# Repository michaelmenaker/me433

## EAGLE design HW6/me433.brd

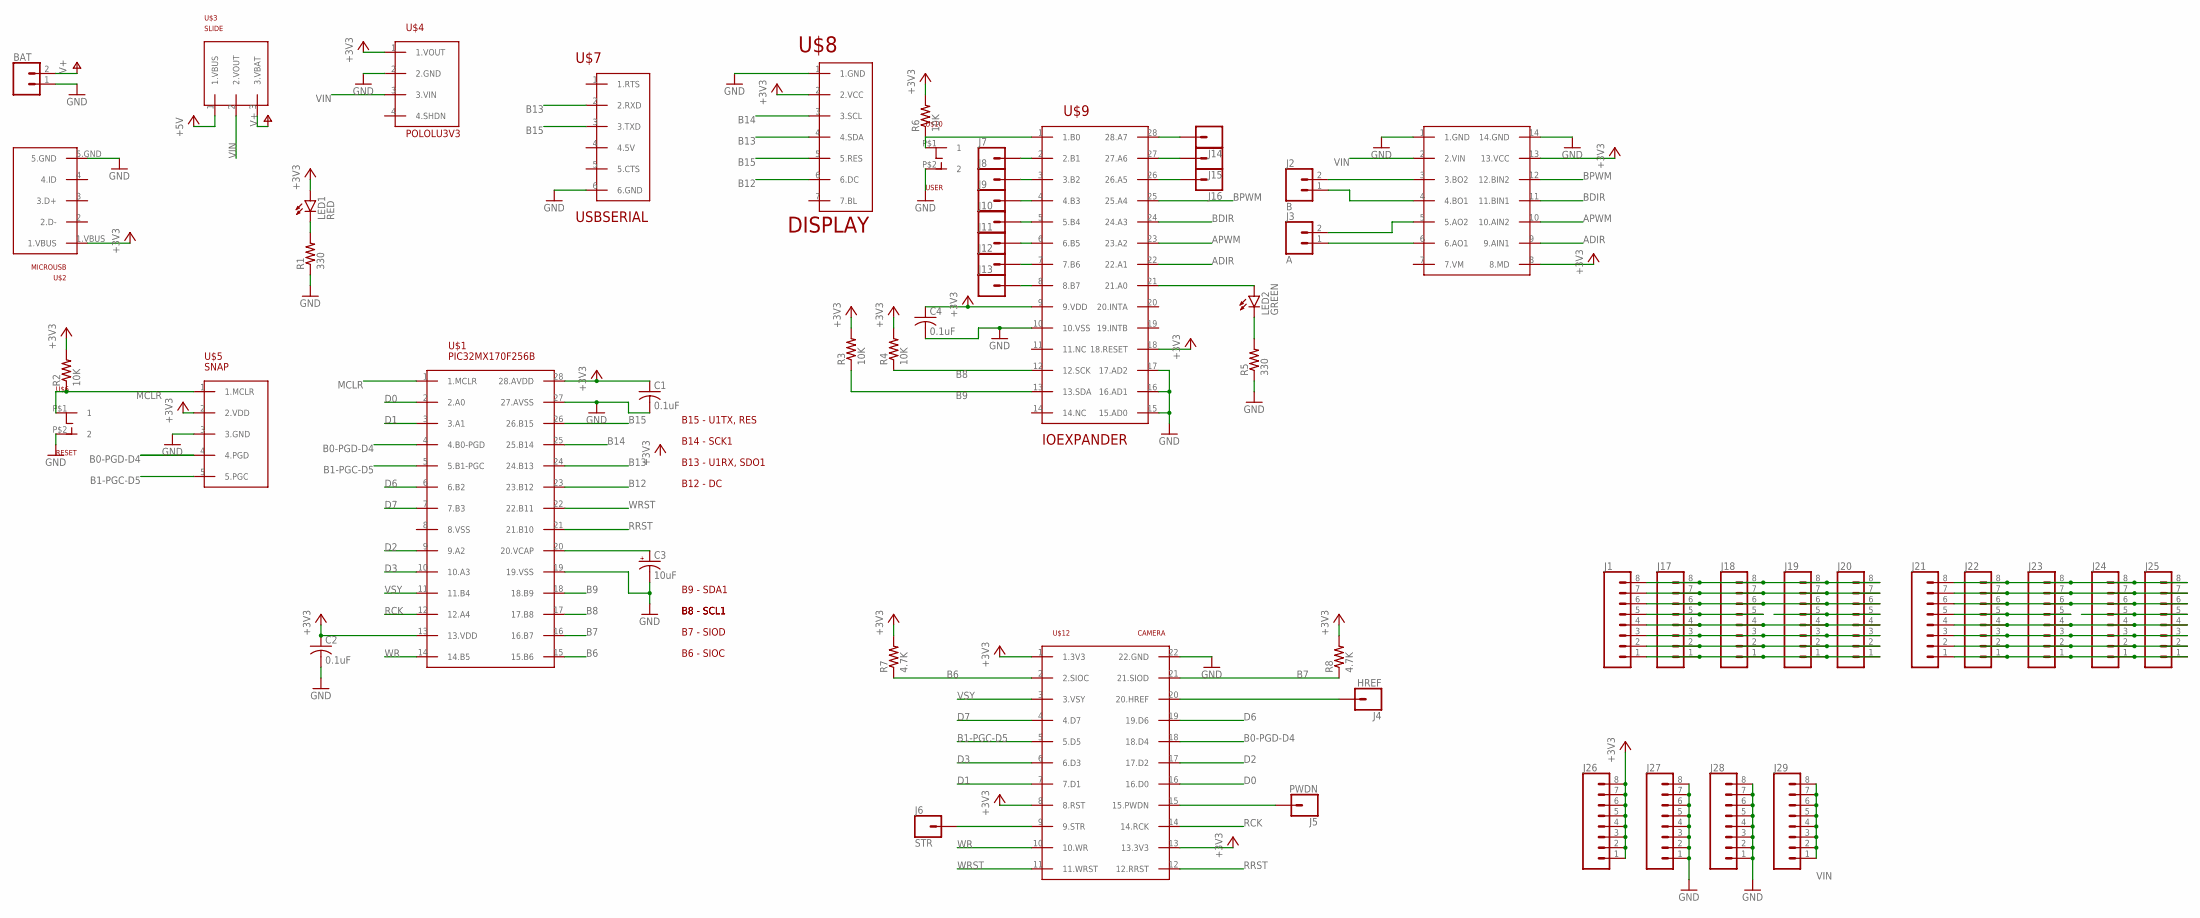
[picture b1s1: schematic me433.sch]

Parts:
BAT: CONN_02; 1X02
C1, C2, C4: 0.1uF; C025-030X050
C3: 10uF; B45181B
J1, J17, J18, J19, J20, J21, J22, J23, J24, J25, J26, J27, J28, J29: CONN_08"; 1X08
J2: B; 1X02
J3: A; 1X02
J4: HREF; 1X01
J5: PWDN; 1X01
J6: STR; 1X01
J7, J8, J9, J10, J11, J12, J13, J14, J15, J16: CONN_01; 1X01
LED1: RED; LED3MM
LED2: GREEN; LED3MM
R1, R5: 330; 0207/10
R2, R3, R4, R6: 10K; 0207/10
R7, R8: 4.7K; 0207/10
U$1: PIC32MX170F256B; DIL28-3
U$2: MICROUSB
U$3: SLIDE
U$4: POLOLU3V3
U$5: SNAP
U$6: RESET; PUSH
U$7: USBSERIAL
U$8: DISPLAY
U$9: IOEXPANDER
U$10: USER; PUSH
U$11: HBRIDGE
U$12: CAMERA

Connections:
+3V1: LED2.A, U$9.21 (21.A0)
+3V3: C1.1, C2.1, C4.1, J26.1, J26.2, J26.3, J26.4, J26.5, J26.6, J26.7, J26.8, LED1.A, R2.2, R3.2, R4.2, R6.2, R7.2, R8.2, U$1.13 (13.VDD), U$1.28 (28.AVDD), U$2.1.VBUS, U$4.1 (1.VOUT), U$5.2 (2.VDD), U$8.2 (2.VCC), U$9.9 (9.VDD), U$9.18 (18.RESET), U$11.8 (8.MD), U$11.13 (13.VCC), U$12.1 (1.3V3), U$12.8 (8.RST), U$12.13 (13.3V3)
+5V: U$3.1 (1.VBUS)
ADIR: U$9.22 (22.A1), U$11.9 (9.AIN1)
APWM: U$9.23 (23.A2), U$11.10 (10.AIN2)
B0-PGD-D4: U$1.4 (4.B0-PGD), U$5.4 (4.PGD), U$12.18 (18.D4)
B1-PGC-D5: U$1.5 (5.B1-PGC), U$5.5 (5.PGC), U$12.5 (5.D5)
B6: R7.1, U$1.15 (15.B6), U$12.2 (2.SIOC)
B7: R8.1, U$1.16 (16.B7), U$12.21 (21.SIOD)
B8: R4.1, U$1.17 (17.B8), U$9.12 (12.SCK)
B9: R3.1, U$1.18 (18.B9), U$9.13 (13.SDA)
B12: U$1.23 (23.B12), U$8.6 (6.DC)
B13: U$1.24 (24.B13), U$7.2 (2.RXD), U$8.4 (4.SDA)
B14: U$1.25 (25.B14), U$8.3 (3.SCL)
B15: U$1.26 (26.B15), U$7.3 (3.TXD), U$8.5 (5.RES)
BDIR: U$9.24 (24.A3), U$11.11 (11.BIN1)
BPWM: U$9.25 (25.A4), U$11.12 (12.BIN2)
D0: U$1.2 (2.A0), U$12.16 (16.D0)
D1: U$1.3 (3.A1), U$12.7 (7.D1)
D2: U$1.9 (9.A2), U$12.17 (17.D2)
D3: U$1.10 (10.A3), U$12.6 (6.D3)
D6: U$1.6 (6.B2), U$12.19 (19.D6)
D7: U$1.7 (7.B3), U$12.4 (4.D7)
GND: BAT.1, C1.2, C2.2, C3.-, C4.2, J27.1, J27.2, J27.3, J27.4, J27.5, J27.6, J27.7, J27.8, J28.1, J28.2, J28.3, J28.4, J28.5, J28.6, J28.7, J28.8, R1.1, R5.1, U$1.19 (19.VSS), U$1.27 (27.AVSS), U$2.5.GND, U$4.2 (2.GND), U$5.3 (3.GND), U$6.P$2 (2), U$7.6 (6.GND), U$8.1 (1.GND), U$9.10 (10.VSS), U$9.15 (15.AD0), U$9.16 (16.AD1), U$9.17 (17.AD2), U$10.P$2 (2), U$11.1 (1.GND), U$11.14 (14.GND), U$12.22 (22.GND)
MCLR: R2.1, U$1.1 (1.MCLR), U$5.1 (1.MCLR), U$6.P$1 (1)
MCLR1: U$10.P$1 (1)
unnamed: LED1.K (C), R1.2
unnamed: C3.+, U$1.20 (20.VCAP)
unnamed: J2.2, U$11.3 (3.BO2)
unnamed: J2.1, U$11.4 (4.BO1)
unnamed: R6.1, U$9.1 (1.B0)
unnamed: LED2.K (C), R5.2
unnamed: J3.2, U$11.5 (5.AO2)
unnamed: J3.1, U$11.6 (6.AO1)
unnamed: J4.1, U$12.20 (20.HREF)
unnamed: J5.1, U$12.15 (15.PWDN)
unnamed: J6.1, U$12.9 (9.STR)
unnamed: J14.1, U$9.28 (28.A7)
unnamed: J15.1, U$9.27 (27.A6)
unnamed: J16.1, U$9.26 (26.A5)
unnamed: J7.1, U$9.2 (2.B1)
unnamed: J8.1, U$9.3 (3.B2)
unnamed: J9.1, U$9.4 (4.B3)
unnamed: J10.1, U$9.5 (5.B4)
unnamed: J11.1, U$9.6 (6.B5)
unnamed: J12.1, U$9.7 (7.B6)
unnamed: J13.1, U$9.8 (8.B7)
unnamed: J1.8, J17.8, J18.8, J19.8, J20.8
unnamed: J1.7, J17.7, J18.7, J19.7, J20.7
unnamed: J1.6, J17.6, J18.6, J19.6, J20.6
unnamed: J1.5, J17.5, J18.5
unnamed: J19.5, J20.5
unnamed: J1.4, J17.4, J18.4, J19.4, J20.4
unnamed: J1.3, J17.3, J18.3, J19.3, J20.3
unnamed: J1.2, J17.2, J18.2, J19.2, J20.2
unnamed: J1.1, J17.1, J18.1, J19.1, J20.1
unnamed: J21.8, J22.8, J23.8, J24.8, J25.8
unnamed: J21.7, J22.7, J23.7, J24.7, J25.7
unnamed: J21.6, J22.6, J23.6, J24.6, J25.6
unnamed: J21.5, J22.5, J23.5
unnamed: J24.5, J25.5
unnamed: J21.4, J22.4, J23.4, J24.4, J25.4
unnamed: J21.3, J22.3, J23.3, J24.3, J25.3
unnamed: J21.2, J22.2, J23.2, J24.2, J25.2
unnamed: J21.1, J22.1, J23.1, J24.1, J25.1
RCK: U$1.12 (12.A4), U$12.14 (14.RCK)
RRST: U$1.21 (21.B10), U$12.12 (12.RRST)
V+: BAT.2, U$3.3 (3.VBAT)
VIN: J29.1, J29.2, J29.3, J29.4, J29.5, J29.6, J29.7, J29.8, U$3.2 (2.VOUT), U$4.3 (3.VIN), U$11.2 (2.VIN)
VSY: U$1.11 (11.B4), U$12.3 (3.VSY)
WR: U$1.14 (14.B5), U$12.10 (10.WR)
WRST: U$1.22 (22.B11), U$12.11 (11.WRST)

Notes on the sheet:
B15 - U1TX, RES
B13 - U1RX, SDO1
B14 - SCK1
B12 - DC
B9 - SDA1
B8 - SCL1
B7 - SIOD
B6 - SIOC

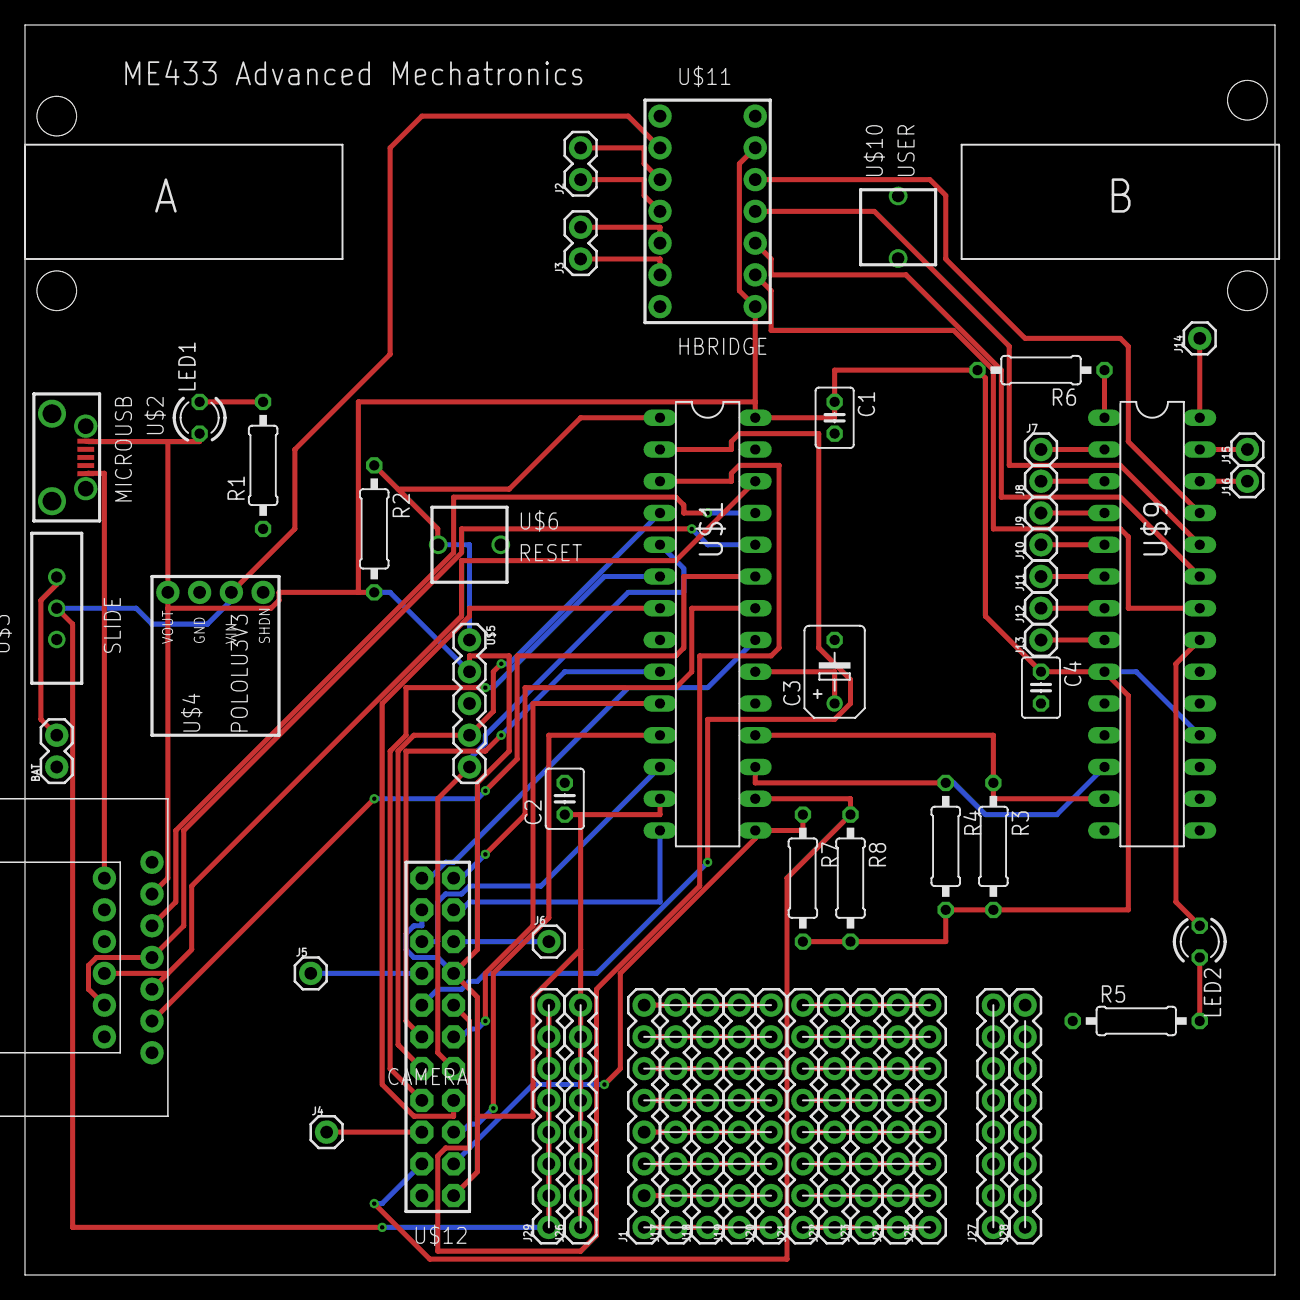
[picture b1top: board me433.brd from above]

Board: 2 copper layers, 100.0 x 100.0 mm, 56 parts (0 on the bottom side), 70 nets.

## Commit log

2021-09-27 Add HW2
2021-09-27 Add HWs

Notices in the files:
parts and their libraries:
SparkFun-Connectors: Licensing: Creative Commons ShareAlike 4.0 International - https://creativecommons.org/licenses/by-sa/4.0
